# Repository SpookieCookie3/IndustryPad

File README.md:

# MatrixPad

A macropad designed in a shape of a industrial radio remote controler. It has six MX-Style switches, one EC11 Rotary encoders, one 0.91 inch OLED display, it's based on the Seeed XIAO RP2040 that uses QMK firmware

It's my first ever project, i had no experience in 3D modeling or making PCB so im quite happy with what i ended up with >u<
I was planning on making some projects including 3d modeling or arduino based elecronics for way too long so this blueprint project was a great push for me to start doing something, anything in my free time. <3

The OLED displays an animation of a cat meowing :3

# Features
6 MX-Style switches 

Rotary Encoder

0.91 inch OLED Display

Powered by Seeed XIAO RP2040 

Firmware in QMK

3D Case

2-Layer PCB

# IndustryPad build

# Schematic and PCB

# BOM
index | Name | Quantity
--- | --- | ---
1 | Diode 1N4148 DO-35| 7
2 | Seeed XIAO RP2040 | 1
3 | MX-Style switches | 6
4 | EC11 Rotary Encoder | 1
5 | 0.91" 128x32 OLED Display (pin order: GND-VCC-SCL-SDA) | 1
6 | M3x16mm screws | 4
7 | M3x5mx4mm heatset inserts | 4
8 | White keycaps | 6

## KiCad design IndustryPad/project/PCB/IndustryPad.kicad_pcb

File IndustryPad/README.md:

# IndustryPad
My first project: A MakroPad designed to look like an industrial radio remote controller

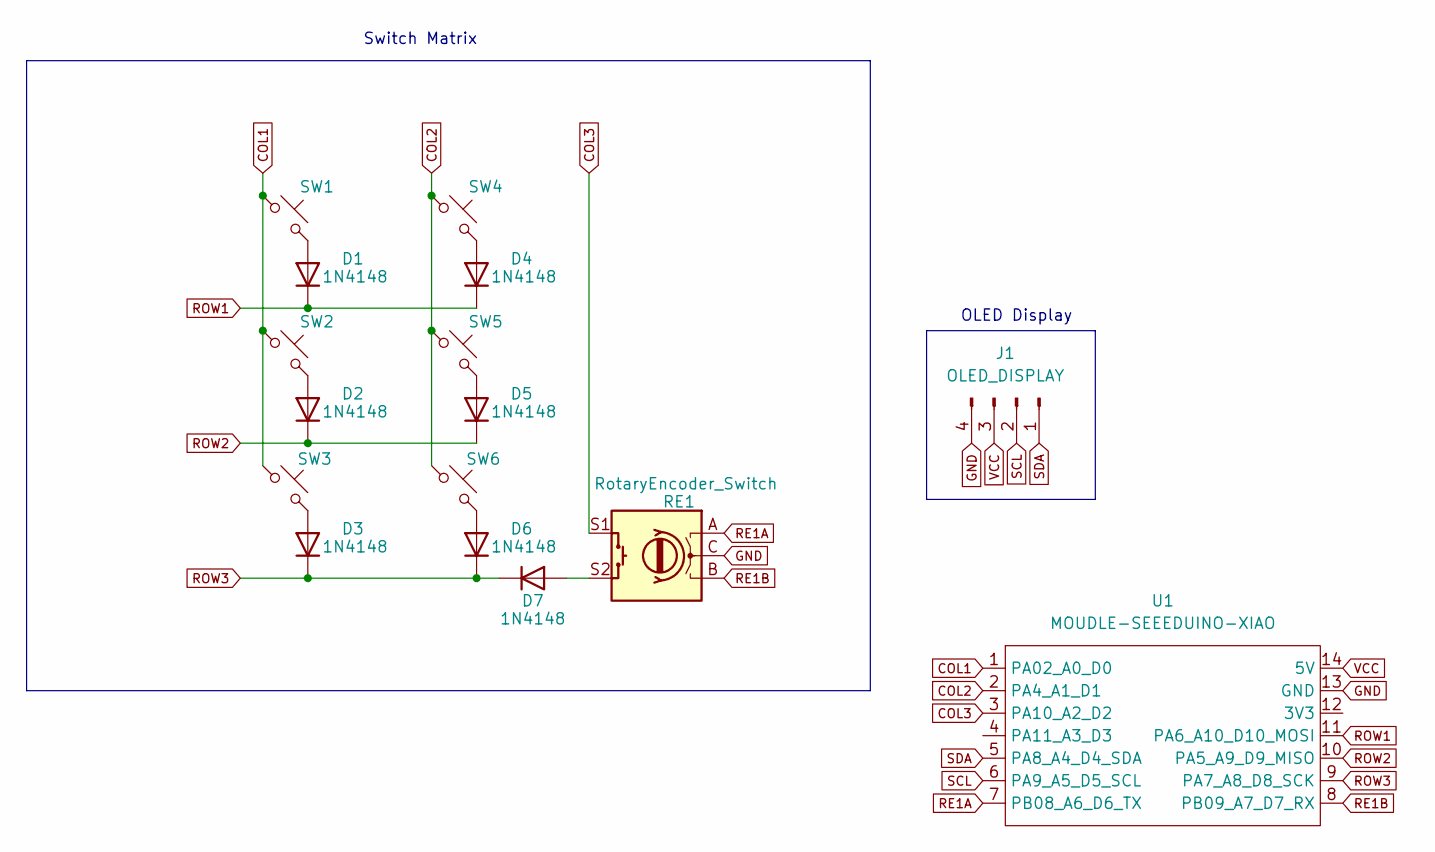
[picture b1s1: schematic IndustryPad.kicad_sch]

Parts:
D1, D2, D3, D4, D5, D6, D7: 1N4148; D_DO-35_SOD27_P7.62mm_Horizontal
J1: OLED_DISPLAY; PinHeader_1x04_P2.54mm_Vertical
RE1: RotaryEncoder_Switch; RotaryEncoder_Alps_EC11E-Switch_Vertical_H20mm
SW1, SW2, SW3, SW4, SW5, SW6: SW_Push_45deg; SW_Cherry_MX_1.00u_PCB
U1: MOUDLE-SEEEDUINO-XIAO; XIAO-Generic-Hybrid-14P-2.54-21X17.8MM

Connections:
COL1: SW1.1, SW2.1, SW3.1, U1.1 (PA02_A0_D0)
COL2: SW4.1, SW5.1, SW6.1, U1.2 (PA4_A1_D1)
COL3: RE1.S1, U1.3 (PA10_A2_D2)
GND: J1.4, RE1.C, U1.13 (GND)
unnamed: D1.2 (A), SW1.2
unnamed: D2.2 (A), SW2.2
unnamed: D3.2 (A), SW3.2
unnamed: D4.2 (A), SW4.2
unnamed: D5.2 (A), SW5.2
unnamed: D6.2 (A), SW6.2
unnamed: D7.2 (A), RE1.S2
RE1A: RE1.A, U1.7 (PB08_A6_D6_TX)
RE1B: RE1.B, U1.8 (PB09_A7_D7_RX)
ROW1: D1.1 (K), D4.1 (K), U1.11 (PA6_A10_D10_MOSI)
ROW2: D2.1 (K), D5.1 (K), U1.10 (PA5_A9_D9_MISO)
ROW3: D3.1 (K), D6.1 (K), D7.1 (K), U1.9 (PA7_A8_D8_SCK)
SCL: J1.2, U1.6 (PA9_A5_D5_SCL)
SDA: J1.1, U1.5 (PA8_A4_D4_SDA)
VCC: J1.3, U1.14 (5V)

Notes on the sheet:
OLED Display
Switch Matrix

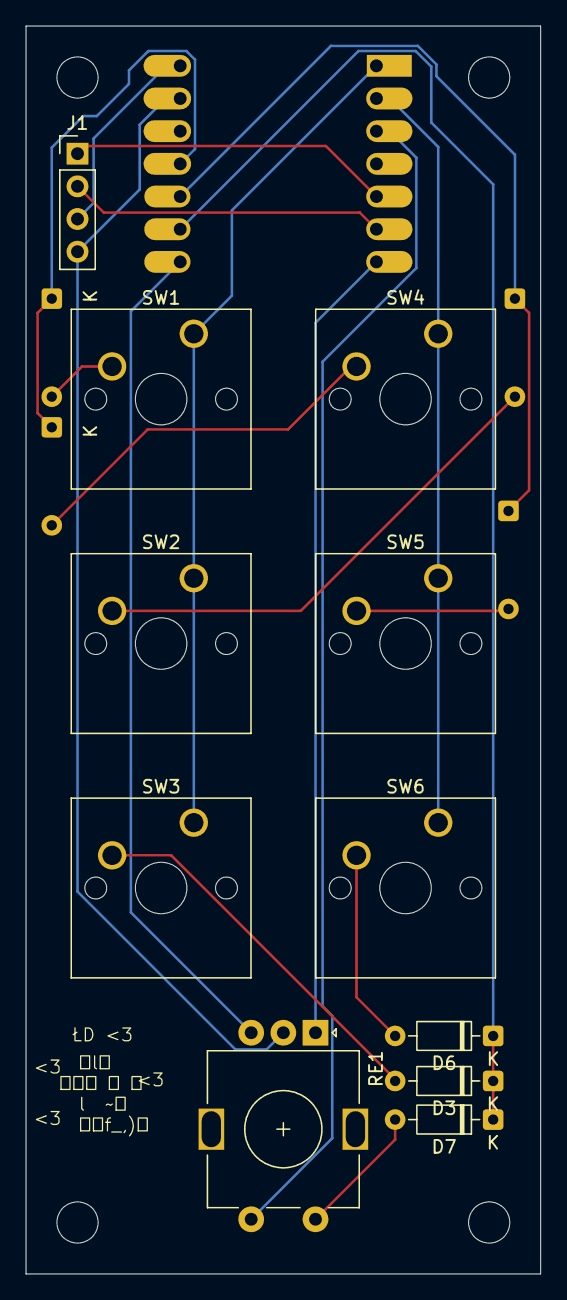
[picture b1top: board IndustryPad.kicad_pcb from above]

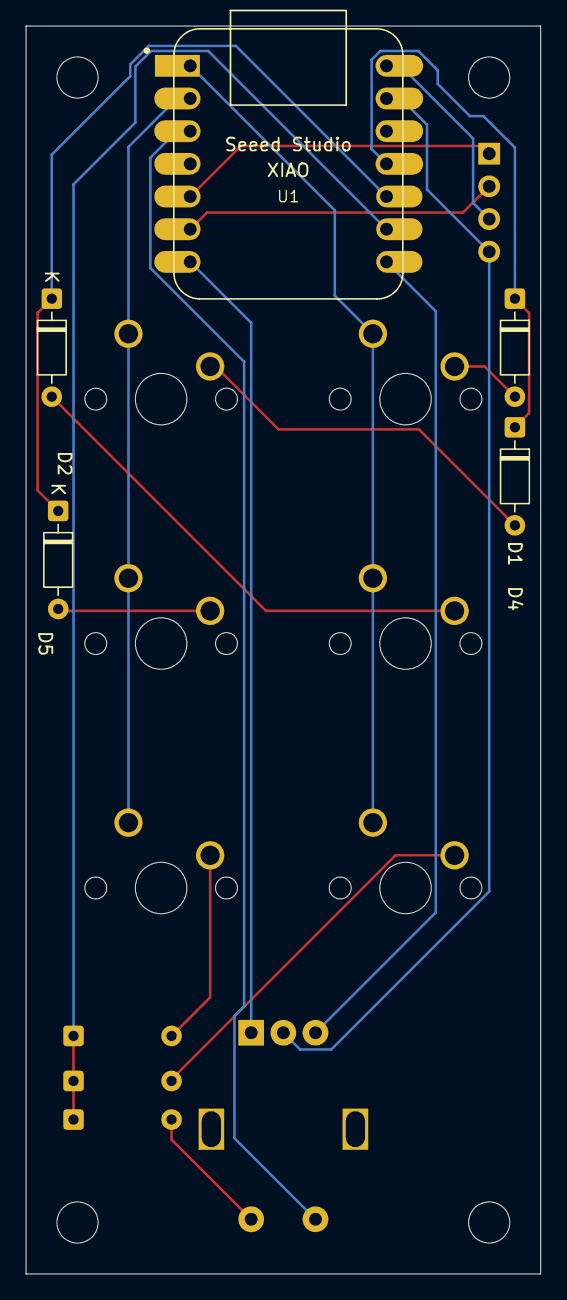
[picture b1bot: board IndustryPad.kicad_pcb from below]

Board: 2 copper layers, 40.0 x 97.0 mm, 16 parts (5 on the bottom side), 19 nets.
